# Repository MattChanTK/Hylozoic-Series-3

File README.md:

Hylozoic Series 3 Interactive Control System
======================

 Combining techniques in architecture, the arts, electronics, and software, the Living Architecture System Group (LASG) develops interactive art sculptures that engage occupants in an immersive environment. The overarching goal of this research is to develop architectural systems that possess life-like qualities. In the Hylozoic Series kinetic sculptures built by [Philip Beesley Architect Inc.](http://philipbeesleyarchitect.com/), the designers use a network of microcontrollers to control and sample a sizable number of actuators and sensors. Each node in the network can perform a simple set of interactive behaviours. Though complexity may emerge in previous systems through superposition of a set of simple and prescripted behaviours, the responses of the systems to occupants remain rather robotic and ultimately dictated by the will of the designers. 

To enable the sculpture to automatically generate interactive behaviours and
adapt to changes, [Curiosity-Based Learning Algorithm (CBLA)](https://ece.uwaterloo.ca/~dkulic/pubs/ChanIROS2015.pdf), a reinforcement learning algorithm which selects actions that lead to maximum potential knowledge gains, is introduced.

To realize the CBLA system on a physical interactive art sculpture, an overhaul of the previous series’ interactive control hardware was necessary. CBLA requires the system to be able to sense the consequences of its own actions and its surrounding at a much higher resolution and frequency than previously implemented behaviour algorithms. This translates to the need to interface and collect samples from a substantially larger number of sensors. 

The **Hylozoic Series 3 Interactive Control System** consists of a new set of hardware and control system software was developed. It enables the control and sampling of hundreds of devices on a centralized computer through USB connections. Moving the computation from an embedded platform simpliﬁes the implementation of the CBLA system, which is a computationally intensive and complex
program. In addition, the large amount of data generated by the system can now be recorded without sacriﬁcing response time nor resolution.

## Organizations

### Hardware

The electronics that interface with the sensors and actuators were mostly customly designed. The [schematic](Hardware/Design Files), [PCB design](Hardware/Design Files), BOM, as well as [fabrication files](Hardware/fabrication) (like Gerber and quotes) for previous production runs can be found in the [Hardware](Hardware) directory. 

### Software

The [firmware](Software/teensy_firmware) that runs on the Teensy microcontroller, the [Python-based software framework](Software/pyHylozoic3) (pyHylozoic3), and [installation-specific behaviours](Software/complex_behaviours) can be found in the [Software](Software) directory. In addition, some of the necessary [libraries](Software/_libraries), and some [basic demo codes](Software/basic_behaviours) can also be in the directory.

In addition to the [communication framework](Software/pyHylozoic3/interactive_system/interactive_system), the pyHylozoic3 module includes an implemenation of the [CBLA Engine](Software/pyHylozoic3/cbla/cbla/cbla_engine), and [Abstract Node system](Software/pyHylozoic3/abstract_node/abstract_node) that supports the deployments of a network of multiple [CBLA Nodes](Software/pyHylozoic3/cbla/cbla).

## Contributors
* Matthew Tsz Kiu Chan (University of Waterloo)
* Mohammedreza Memarian (University of Waterloo)
* Matt Borland (Philip Beesley Architect Inc.)
* David Kadish (Philip Beesley Architect Inc.)

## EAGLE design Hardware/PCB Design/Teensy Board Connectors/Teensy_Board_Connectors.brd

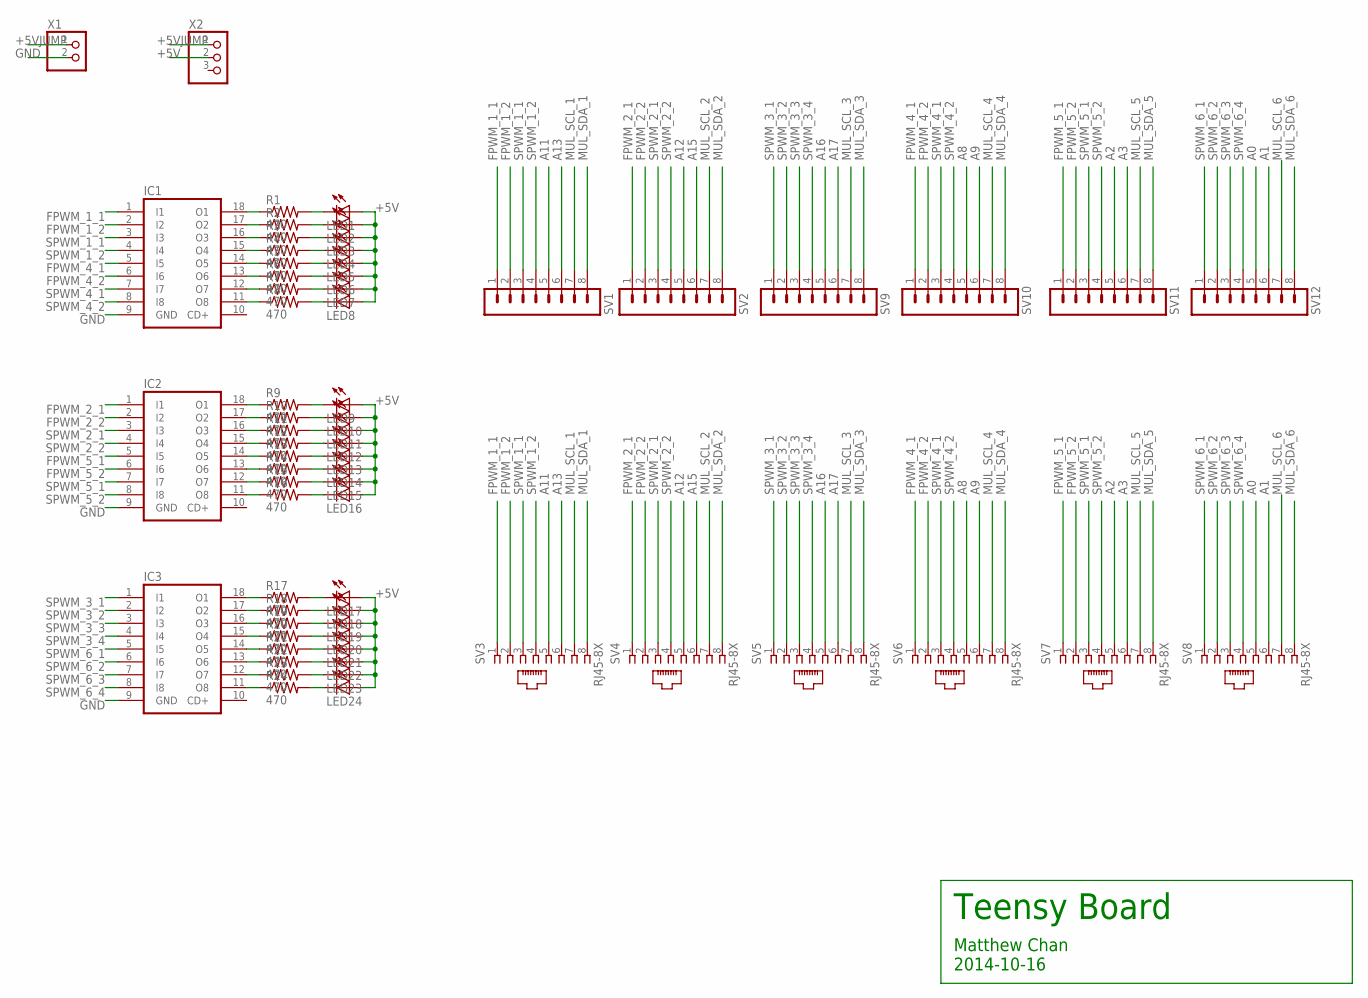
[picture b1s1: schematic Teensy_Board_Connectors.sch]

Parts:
IC1, IC2, IC3: ULN2803AFWG; SOP18
LED1, LED2, LED3, LED4, LED5, LED6, LED7, LED8, LED9, LED10, LED11, LED12, LED13, LED14, LED15, LED16, LED17, LED18, LED19, LED20, LED21, LED22, LED23, LED24: LEDSML1206; SML1206
R1, R2, R3, R4, R5, R6, R7, R8, R9, R10, R11, R12, R13, R14, R15, R16, R17, R18, R19, R20, R21, R22, R23, R24: 470; R0603
SV1, SV2, SV9, SV10, SV11, SV12: MA08-1
SV3, SV4, SV5, SV6, SV7, SV8: RJ45-8X; RJ45-NO-SHIELD
X1: PINHD-1X2; 1X02
X2: PINHD-1X3; 1X03

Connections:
+5V: LED1.A, LED2.A, LED3.A, LED4.A, LED5.A, LED6.A, LED7.A, LED8.A, LED9.A, LED10.A, LED11.A, LED12.A, LED13.A, LED14.A, LED15.A, LED16.A, LED17.A, LED18.A, LED19.A, LED20.A, LED21.A, LED22.A, LED23.A, LED24.A, X2.2
+5VJUMP: X1.1, X2.1
A0: SV8.5, SV12.5
A1: SV8.6, SV12.6
A2: SV7.5, SV11.5
A3: SV7.6, SV11.6
A8: SV6.5, SV10.5
A9: SV6.6, SV10.6
A11: SV1.5, SV3.5
A12: SV2.5, SV4.5
A13: SV1.6, SV3.6
A15: SV2.6, SV4.6
A16: SV5.5, SV9.5
A17: SV5.6, SV9.6
FPWM_1_1: IC1.1 (I1), SV1.1, SV3.1
FPWM_1_2: IC1.2 (I2), SV1.2, SV3.2
FPWM_2_1: IC2.1 (I1), SV2.1, SV4.1
FPWM_2_2: IC2.2 (I2), SV2.2, SV4.2
FPWM_4_1: IC1.5 (I5), SV6.1, SV10.1
FPWM_4_2: IC1.6 (I6), SV6.2, SV10.2
FPWM_5_1: IC2.5 (I5), SV7.1, SV11.1
FPWM_5_2: IC2.6 (I6), SV7.2, SV11.2
GND: IC1.9 (GND), IC2.9 (GND), IC3.9 (GND), X1.2
MUL_SCL_1: SV1.7, SV3.7
MUL_SCL_2: SV2.7, SV4.7
MUL_SCL_3: SV5.7, SV9.7
MUL_SCL_4: SV6.7, SV10.7
MUL_SCL_5: SV7.7, SV11.7
MUL_SCL_6: SV8.7, SV12.7
MUL_SDA_1: SV1.8, SV3.8
MUL_SDA_2: SV2.8, SV4.8
MUL_SDA_3: SV5.8, SV9.8
MUL_SDA_4: SV6.8, SV10.8
MUL_SDA_5: SV7.8, SV11.8
MUL_SDA_6: SV8.8, SV12.8
unnamed: IC1.18 (O1), R1.1
unnamed: LED1.C, R1.2
unnamed: IC1.17 (O2), R2.1
unnamed: IC1.16 (O3), R3.1
unnamed: IC1.15 (O4), R4.1
unnamed: IC1.14 (O5), R5.1
unnamed: IC1.13 (O6), R6.1
unnamed: IC1.12 (O7), R7.1
unnamed: IC1.11 (O8), R8.1
unnamed: LED2.C, R2.2
unnamed: LED3.C, R3.2
unnamed: LED4.C, R4.2
unnamed: LED5.C, R5.2
unnamed: LED6.C, R6.2
unnamed: LED7.C, R7.2
unnamed: LED8.C, R8.2
unnamed: IC2.18 (O1), R9.1
unnamed: LED9.C, R9.2
unnamed: IC2.17 (O2), R10.1
unnamed: IC2.16 (O3), R11.1
unnamed: IC2.15 (O4), R12.1
unnamed: IC2.14 (O5), R13.1
unnamed: IC2.13 (O6), R14.1
unnamed: IC2.12 (O7), R15.1
unnamed: IC2.11 (O8), R16.1
unnamed: LED10.C, R10.2
unnamed: LED11.C, R11.2
unnamed: LED12.C, R12.2
unnamed: LED13.C, R13.2
unnamed: LED14.C, R14.2
unnamed: LED15.C, R15.2
unnamed: LED16.C, R16.2
unnamed: IC3.18 (O1), R17.1
unnamed: LED17.C, R17.2
unnamed: IC3.17 (O2), R18.1
unnamed: IC3.16 (O3), R19.1
unnamed: IC3.15 (O4), R20.1
unnamed: IC3.14 (O5), R21.1
unnamed: IC3.13 (O6), R22.1
unnamed: IC3.12 (O7), R23.1
unnamed: IC3.11 (O8), R24.1
unnamed: LED18.C, R18.2
unnamed: LED19.C, R19.2
unnamed: LED20.C, R20.2
unnamed: LED21.C, R21.2
unnamed: LED22.C, R22.2
unnamed: LED23.C, R23.2
unnamed: LED24.C, R24.2
SPWM_1_1: IC1.3 (I3), SV1.3, SV3.3
SPWM_1_2: IC1.4 (I4), SV1.4, SV3.4
SPWM_2_1: IC2.3 (I3), SV2.3, SV4.3
SPWM_2_2: IC2.4 (I4), SV2.4, SV4.4
SPWM_3_1: IC3.1 (I1), SV5.1, SV9.1
SPWM_3_2: IC3.2 (I2), SV5.2, SV9.2
SPWM_3_3: IC3.3 (I3), SV5.3, SV9.3
SPWM_3_4: IC3.4 (I4), SV5.4, SV9.4
SPWM_4_1: IC1.7 (I7), SV6.3, SV10.3
SPWM_4_2: IC1.8 (I8), SV6.4, SV10.4
SPWM_5_1: IC2.7 (I7), SV7.3, SV11.3
SPWM_5_2: IC2.8 (I8), SV7.4, SV11.4
SPWM_6_1: IC3.5 (I5), SV8.1, SV12.1
SPWM_6_2: IC3.6 (I6), SV8.2, SV12.2
SPWM_6_3: IC3.7 (I7), SV8.3, SV12.3
SPWM_6_4: IC3.8 (I8), SV8.4, SV12.4

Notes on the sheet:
Teensy Board
Matthew Chan 2014-10-16

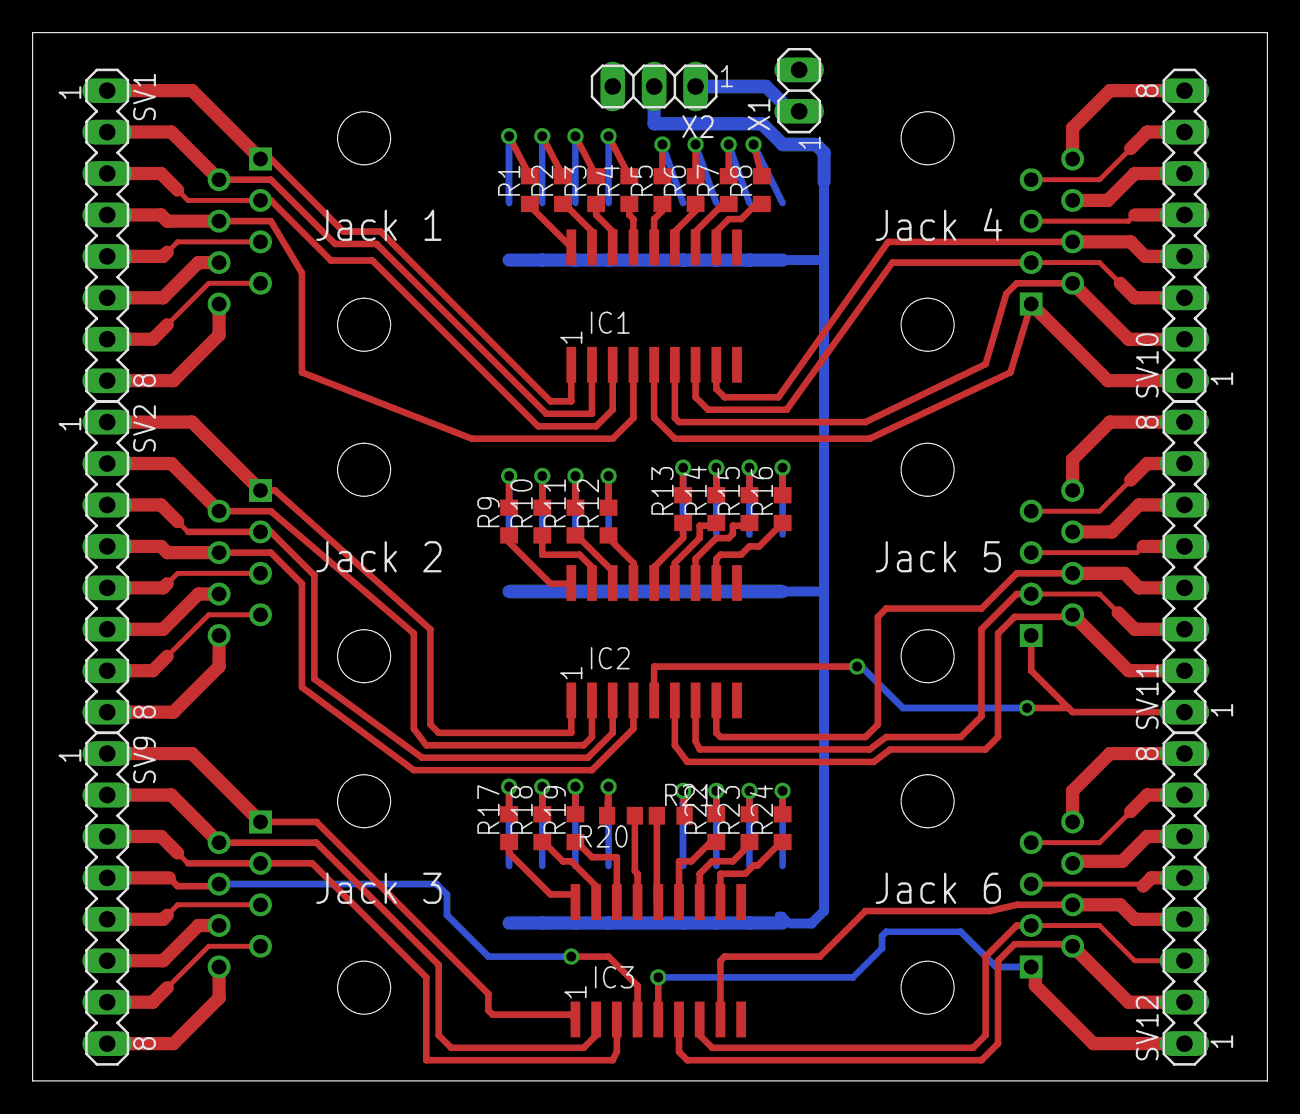
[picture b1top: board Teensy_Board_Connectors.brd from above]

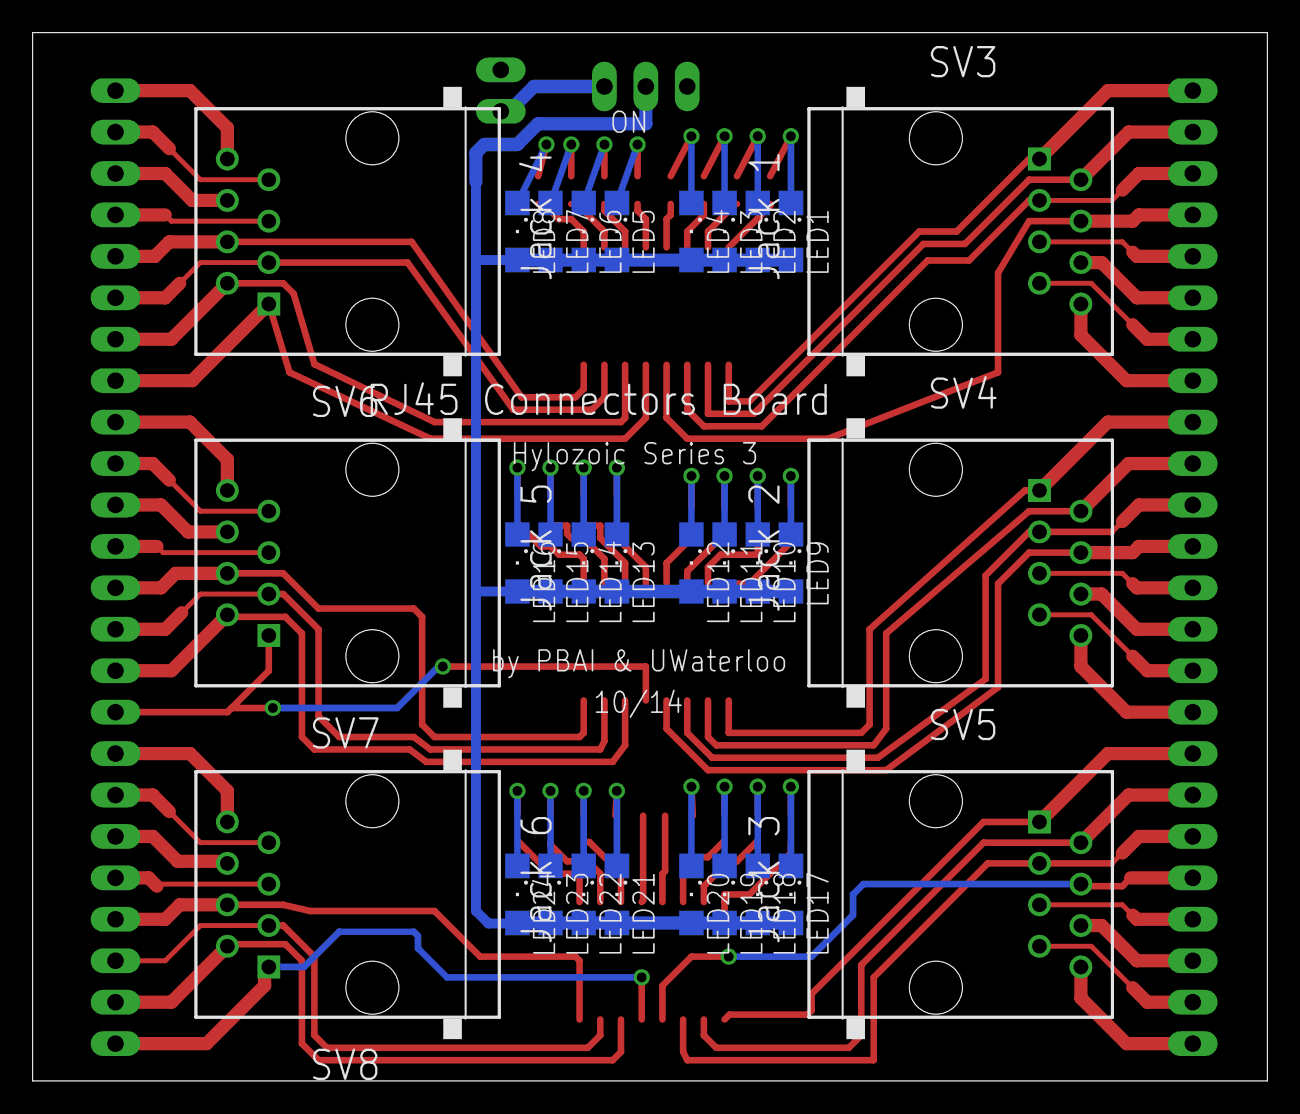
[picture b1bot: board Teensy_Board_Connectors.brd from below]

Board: 2 copper layers, 75.7 x 64.3 mm, 65 parts (30 on the bottom side), 99 nets.

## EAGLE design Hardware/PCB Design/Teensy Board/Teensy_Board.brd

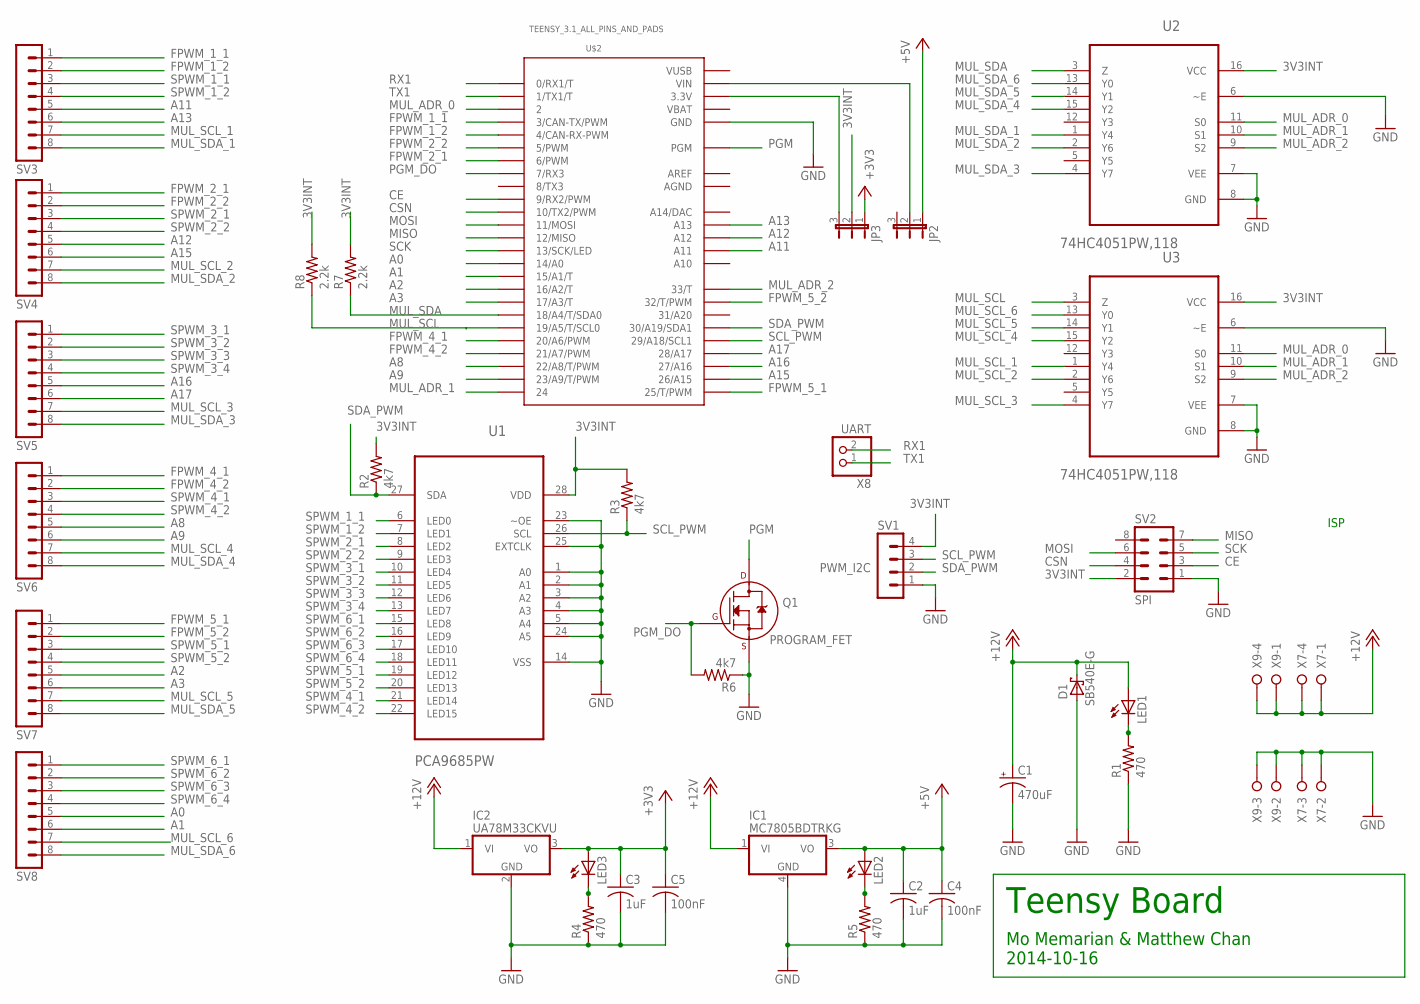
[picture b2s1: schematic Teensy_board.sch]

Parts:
C1: 470uF; E5-10,5
C2, C3: 1uF; C0603
C4, C5: 100nF; C0603
D1: SB540E-G; DO201T15
IC1: MC7805BDTRKG; DPACK_3
IC2: UA78M33CKVU; DPACK
JP2, JP3: JP2E; JP2
LED1, LED2, LED3: LEDSML1206; SML1206
Q1: PROGRAM_FET; SOT-23
R1, R4, R5: 470; R0603
R2, R3, R6: 4k7; R0603
R7, R8: 2.2k; R0603
SV1: PWM_I2C; MA04-1
SV2: SPI; MA04-2
SV3, SV4, SV5, SV6, SV7, SV8: MA08-1
U1: PCA9685PW; SOP65P640X110-28N
U2, U3: 74HC4051PW,118; SOP65P640X110-16N
U$2: TEENSY_3.1_ALL_PINS_AND_PADS; TEENSY_3.1_ALLPINS
X7, X9: W237-04P; W237-4P
X8: UART; 1X02

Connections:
3V3INT: JP3.2, R2.2, R3.2, R7.2, R8.2, SV1.4, SV2.2, U1.28 (VDD), U2.16 (VCC), U3.16 (VCC)
+3V3: C3.1, C5.1, IC2.3 (VO), JP3.1, LED3.A
+5V: C2.1, C4.1, IC1.3 (VO), JP2.1, LED2.A
+12V: C1.+, D1.C, IC1.1 (VI), IC2.1 (VI), LED1.A, X7.1, X7.4, X9.1, X9.4
A0: SV8.5, U$2.14/A0
A1: SV8.6, U$2.15/A1 (15/A1/T)
A2: SV7.5, U$2.16/A2 (16/A2/T)
A3: SV7.6, U$2.17/A3 (17/A3/T)
A8: SV6.5, U$2.22/A8 (22/A8/T/PWM)
A9: SV6.6, U$2.23/A9 (23/A9/T/PWM)
A11: SV3.5, U$2.A11
A12: SV4.5, U$2.A12
A13: SV3.6, U$2.A13
A15: SV4.6, U$2.26 (26/A15)
A16: SV5.5, U$2.27 (27/A16)
A17: SV5.6, U$2.28 (28/A17)
AGND: U$2.AGND
AREF: U$2.AREF
CE: SV2.3, U$2.9 (9/RX2/PWM)
CSN: SV2.4, U$2.10 (10/TX2/PWM)
FPWM_1_1: SV3.1, U$2.3 (3/CAN-TX/PWM)
FPWM_1_2: SV3.2, U$2.4 (4/CAN-RX-PWM)
FPWM_2_1: SV4.1, U$2.6 (6/PWM)
FPWM_2_2: SV4.2, U$2.5 (5/PWM)
FPWM_4_1: SV6.1, U$2.20/A6 (20/A6/PWM)
FPWM_4_2: SV6.2, U$2.21/A7 (21/A7/PWM)
FPWM_5_1: SV7.1, U$2.25 (25/T/PWM)
FPWM_5_2: SV7.2, U$2.32 (32/T/PWM)
GND: C1.-, C2.2, C3.2, C4.2, C5.2, D1.A, IC1.4 (GND), IC2.2 (GND), Q1.2 (S), R1.1, R4.1, R5.1, R6.1, SV1.1, SV2.1, U1.1 (A0), U1.2 (A1), U1.3 (A2), U1.4 (A3), U1.5 (A4), U1.14 (VSS), U1.23 (~OE), U1.24 (A5), U1.25 (EXTCLK), U2.6 (~E), U2.7 (VEE), U2.8 (GND), U3.6 (~E), U3.7 (VEE), U3.8 (GND), U$2.GND, U$2.GND1 (GND), U$2.GND2 (GND), X7.2, X7.3, X9.2, X9.3; also elsewhere on the board
MISO: SV2.7, U$2.12 (12/MISO)
MOSI: SV2.6, U$2.11 (11/MOSI)
MUL_ADR_0: U2.11 (S0), U3.11 (S0), U$2.2
MUL_ADR_1: U2.10 (S1), U3.10 (S1), U$2.24
MUL_ADR_2: U2.9 (S2), U3.9 (S2), U$2.33 (33/T)
MUL_SCL: R8.1, U3.3 (Z), U$2.19/A5 (19/A5/T/SCL0)
MUL_SCL_1: SV3.7, U3.1 (Y4)
MUL_SCL_2: SV4.7, U3.2 (Y6)
MUL_SCL_3: SV5.7, U3.4 (Y7)
MUL_SCL_4: SV6.7, U3.15 (Y2)
MUL_SCL_5: SV7.7, U3.14 (Y1)
MUL_SCL_6: SV8.7, U3.13 (Y0)
MUL_SDA: R7.1, U2.3 (Z), U$2.18/A4 (18/A4/T/SDA0)
MUL_SDA_1: SV3.8, U2.1 (Y4)
MUL_SDA_2: SV4.8, U2.2 (Y6)
MUL_SDA_3: SV5.8, U2.4 (Y7)
MUL_SDA_4: SV6.8, U2.15 (Y2)
MUL_SDA_5: SV7.8, U2.14 (Y1)
MUL_SDA_6: SV8.8, U2.13 (Y0)
unnamed: LED1.C, R1.2
unnamed: LED3.C, R4.2
unnamed: LED2.C, R5.2
PGM: Q1.3 (D), U$2.PGM
PGM_DO: Q1.1 (G), R6.2, U$2.7 (7/RX3)
RX1: U$2.0 (0/RX1/T), X8.2
SCK: SV2.5, U$2.13 (13/SCK/LED)
SCL_PWM: R3.1, SV1.3, U1.26 (SCL), U$2.29 (29/A18/SCL1)
SDA_PWM: R2.1, SV1.2, U1.27 (SDA), U$2.30 (30/A19/SDA1)
SPWM_1_1: SV3.3, U1.6 (LED0)
SPWM_1_2: SV3.4, U1.7 (LED1)
SPWM_2_1: SV4.3, U1.8 (LED2)
SPWM_2_2: SV4.4, U1.9 (LED3)
SPWM_3_1: SV5.1, U1.10 (LED4)
SPWM_3_2: SV5.2, U1.11 (LED5)
SPWM_3_3: SV5.3, U1.12 (LED6)
SPWM_3_4: SV5.4, U1.13 (LED7)
SPWM_4_1: SV6.3, U1.21 (LED14)
SPWM_4_2: SV6.4, U1.22 (LED15)
SPWM_5_1: SV7.3, U1.19 (LED12)
SPWM_5_2: SV7.4, U1.20 (LED13)
SPWM_6_1: SV8.1, U1.15 (LED8)
SPWM_6_2: SV8.2, U1.16 (LED9)
SPWM_6_3: SV8.3, U1.17 (LED10)
SPWM_6_4: SV8.4, U1.18 (LED11)
TEENSY_3V3: JP3.3, U$2.3.3V, U$2.3.3V1 (3.3V), U$2.3.3V2 (3.3V)
TEENSY_VIN: JP2.2, U$2.VIN; also elsewhere on the board
TX1: U$2.1 (1/TX1/T), X8.1
VBAT: U$2.VBAT
VUSB: U$2.VUSB

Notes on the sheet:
Teensy Board
Mo Memarian & Matthew Chan 2014-10-16
ISP

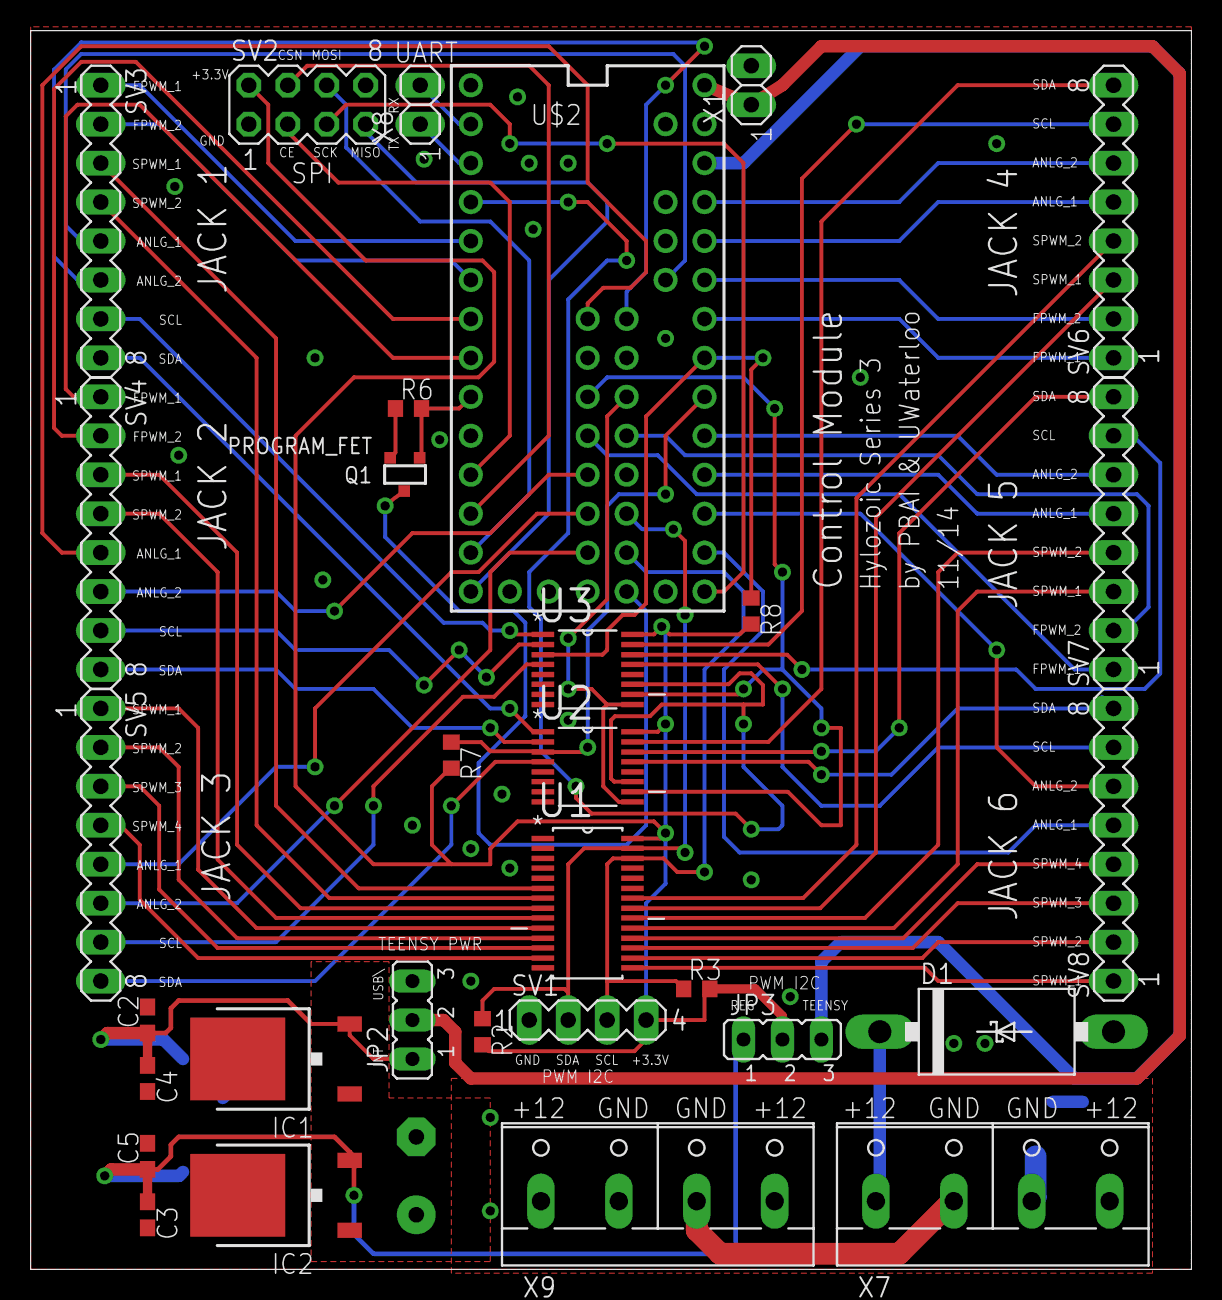
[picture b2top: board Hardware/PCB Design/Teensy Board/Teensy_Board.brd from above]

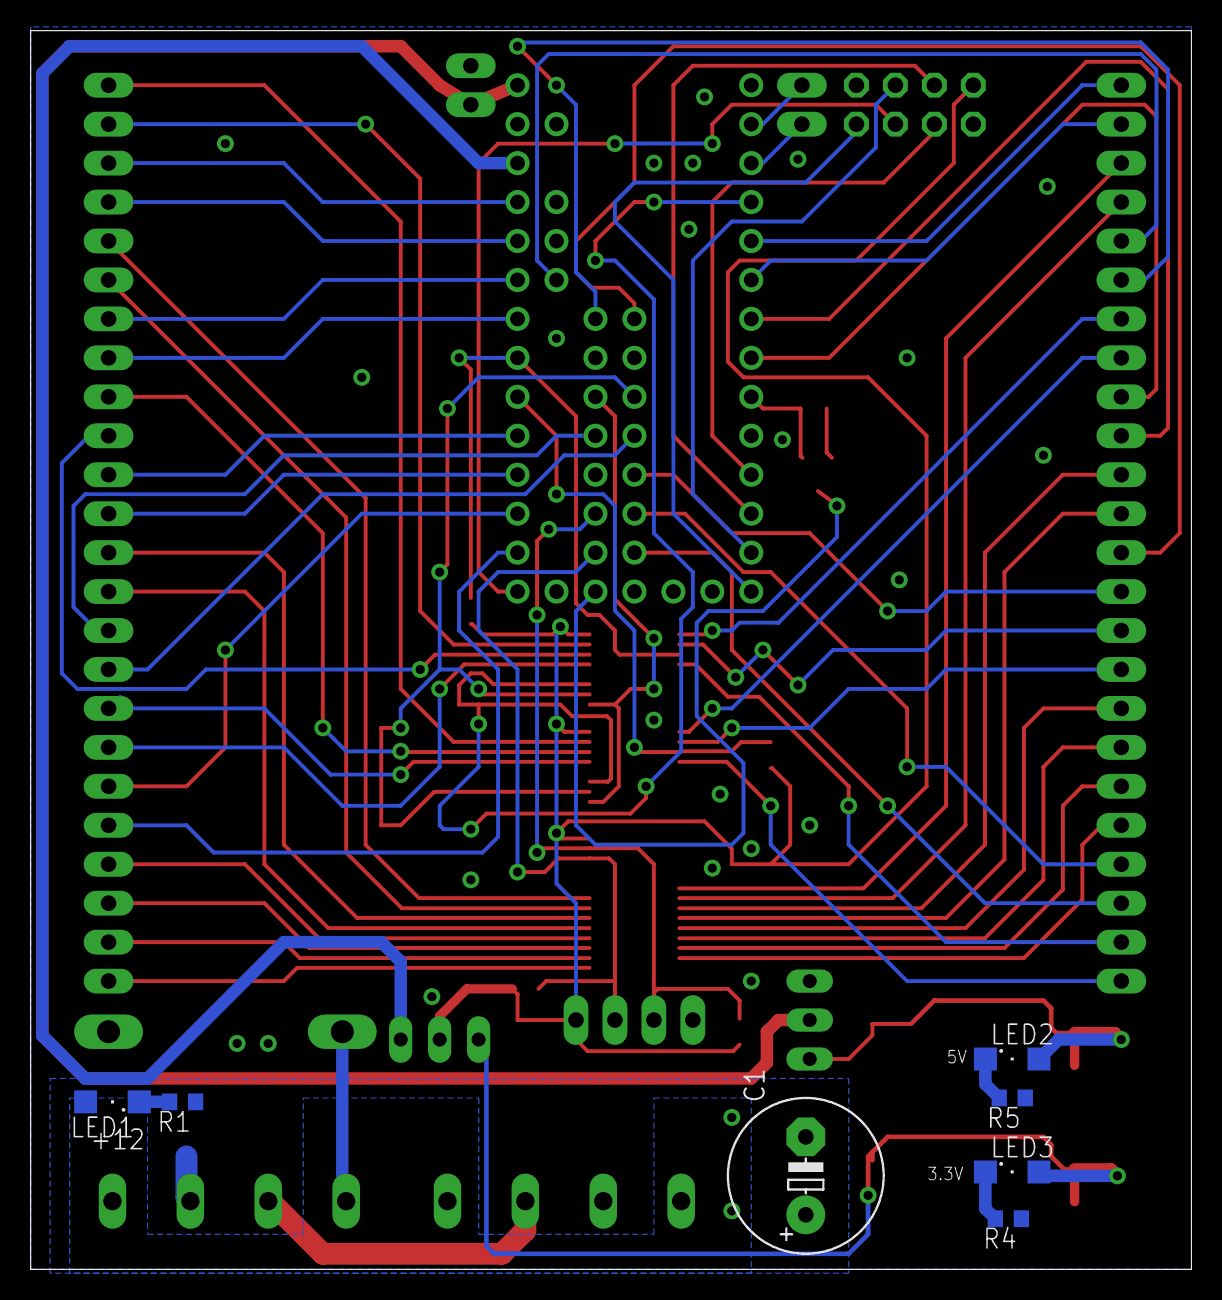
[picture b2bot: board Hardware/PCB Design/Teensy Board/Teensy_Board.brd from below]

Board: 2 copper layers, 75.7 x 80.8 mm, 38 parts (7 on the bottom side), 74 nets.

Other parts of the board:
X1: 1X02

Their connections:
GND: X1.2; also elsewhere on the board
TEENSY_VIN: X1.1; also elsewhere on the board

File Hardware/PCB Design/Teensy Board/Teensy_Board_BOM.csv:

"Qty";"Value";"Device";"Package";"Parts";"Description";"MF";"MPN";"OC_FARNELL";"OC_NEWARK";"PACKAGE";"SUPPLIER";
"2";"";"JP2E";"JP2";"JP2, JP3";"JUMPER";"";"";"";"";"";"";
"3";"";"LEDSML1206";"SML1206";"LED1, LED2, LED3";"LED";"";"";"";"";"";"";
"6";"";"MA08-1";"MA08-1";"SV3, SV4, SV5, SV6, SV7, SV8";"PIN HEADER";"";"";"unknown";"unknown";"";"";
"2";"";"R-US_R0603";"R0603";"R7, R8";"RESISTOR, American symbol";"";"";"";"";"";"";
"3";"";"W237-04P";"W237-4P";"X7, X9, X10";"WAGO SREW CLAMP";"";"";"unknown";"unknown";"";"";
"2";"100nF";"C-USC0603";"C0603";"C4, C5";"CAPACITOR, American symbol";"";"";"";"";"";"";
"2";"1uF";"C-USC0603";"C0603";"C2, C3";"CAPACITOR, American symbol";"";"";"";"";"";"";
"3";"470";"R-US_R0603";"R0603";"R1, R4, R5";"RESISTOR, American symbol";"";"";"";"";"";"";
"1";"470uF";"CPOL-USE5-10.5";"E5-10,5";"C1";"POLARIZED CAPACITOR, American symbol";"";"";"";"";"";"";
"3";"4k7";"R-US_R0603";"R0603";"R2, R3, R6";"RESISTOR, American symbol";"";"";"";"";"";"";
"2";"74HC4051PW,118";"74HC4051PW,118";"SOP65P640X110-16N";"U2, U3";"8-channel analog multiplexer/demultiplexer";"";"74HC4051PW,118";"1826843";"78R6260";"TSSOP-16";"NXP";
"1";"MC7805BDTRKG";"MC7805BDTRKG";"DPACK_3";"IC1";"1A Positive Voltage Regulators";"";"";"";"";"";"";
"1";"PCA9685PW";"PCA9685PW";"SOP65P640X110-28N";"U1";"16-channel, 12-bit PWM Fm+ I2C-bus LED controller";"";"PCA9685PW";"1854074";"19T6398";"TSSOP-28";"NXP";
"1";"PROGRAM_FET";"2N7002_SOT23";"SOT-23";"Q1";"2N7000, 2N7002, NDS7002A";"";"";"";"";"";"";
"1";"PWM_I2C";"MA04-1";"MA04-1";"SV1";"PIN HEADER";"";"";"unknown";"unknown";"";"";
"6";"RJ45-8X";"RJ45-8X";"RJ45-NO-SHIELD";"X1, X2, X3, X4, X5, X6";"CORCOM Modular RJ Jacks No Shield";"";"RJ45-8X";"unknown";"16R6101";"";"";
"1";"SB540E-G";"SB540E-G";"DO201T15";"D1";"SCHOTTKY BARRIER RECTIFIER 3.0 AMPERES 20, 30, 40 VOLT";"";"";"";"";"";"";
"1";"SPI";"MA04-2";"MA04-2";"SV2";"PIN HEADER";"";"";"unknown";"unknown";"";"";
"1";"TEENSY_3.1_ALL_PINS_AND_PADS";"TEENSY_3.1_ALL_PINS_AND_PADS";"TEENSY_3.1_ALLPINS";"U$2";"Footprint for Teensy 3.1 board using all pads and all through-holes. Pads need a 2x7 0.1" SMD header.";"";"";"";"";"";"";
"1";"UA78M33CKVU";"UA78M33CKVU";"DPACK";"IC2";"Linear Voltage Reg";"";"";"";"";"";"";
"1";"UART";"PINHD-1X2";"1X02";"X8";"PIN HEADER";"";"";"";"";"";"";

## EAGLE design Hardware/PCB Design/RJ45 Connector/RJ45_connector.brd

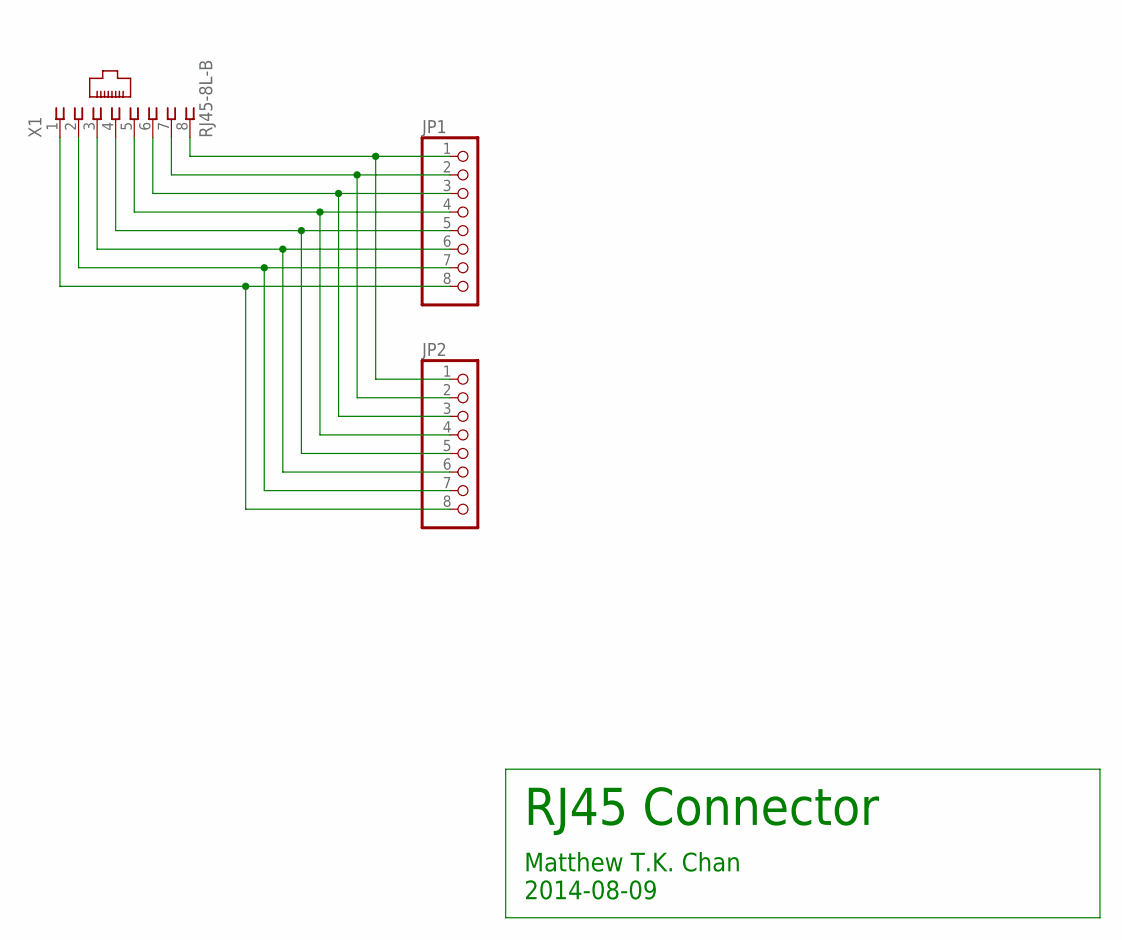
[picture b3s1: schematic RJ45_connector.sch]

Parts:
JP1, JP2: PINHD-1X8/90; 1X08/90
X1: RJ45-8L-B; RJ45-NO-SHIELD

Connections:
unnamed: JP1.1, JP2.1, X1.8
unnamed: JP1.2, JP2.2, X1.7
unnamed: JP1.3, JP2.3, X1.6
unnamed: JP1.4, JP2.4, X1.5
unnamed: JP1.5, JP2.5, X1.4
unnamed: JP1.6, JP2.6, X1.3
unnamed: JP1.7, JP2.7, X1.2
unnamed: JP1.8, JP2.8, X1.1

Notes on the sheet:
RJ45 Connector
Matthew T.K. Chan 2014-08-09

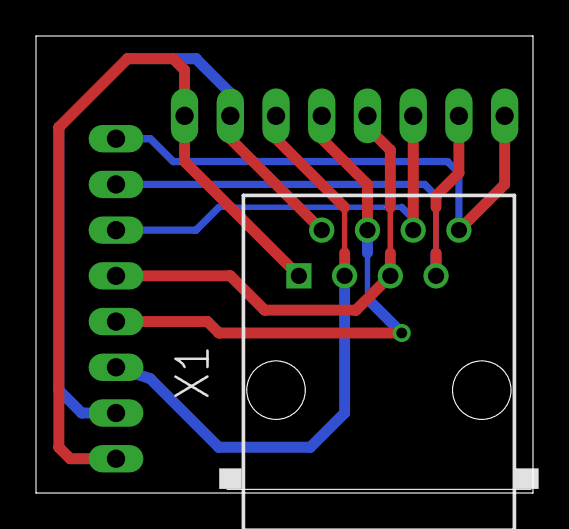
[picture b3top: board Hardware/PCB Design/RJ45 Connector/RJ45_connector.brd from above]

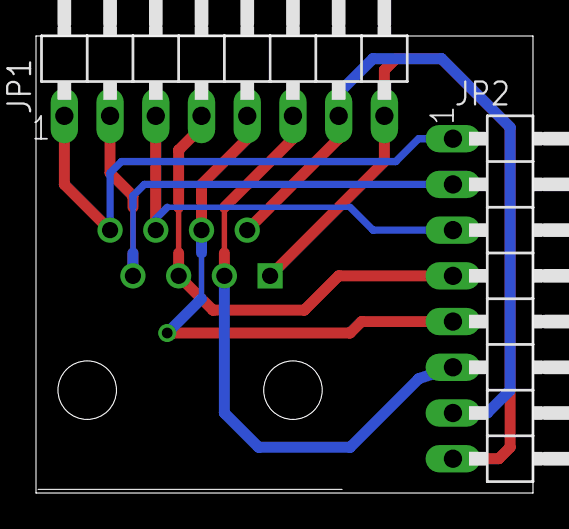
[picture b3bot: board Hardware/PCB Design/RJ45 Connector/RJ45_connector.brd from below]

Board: 2 copper layers, 27.6 x 25.4 mm, 3 parts (2 on the bottom side), 8 nets.

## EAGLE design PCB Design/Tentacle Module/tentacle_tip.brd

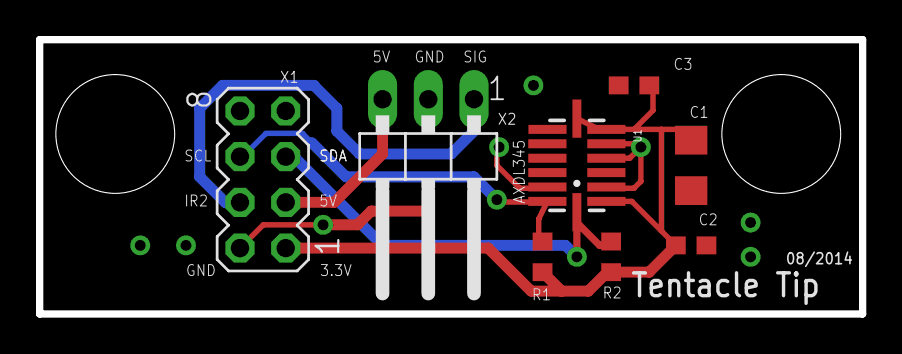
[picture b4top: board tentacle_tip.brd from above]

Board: 2 copper layers, 45.7 x 15.2 mm, 8 parts (0 on the bottom side), 6 nets.

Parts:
C1: 10uF; C1206
C2, C3: 0.1uF; C0603
R1, R2: 2.2k; R0603
U1: ADXL345; LGA14_LONG
X1: MA04-2
X2: 1X03/90

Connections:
+3.3V: C1.1, C2.1, C3.1, R1.2, R2.2, U1.1, U1.6, U1.7, X1.1
+5V: X1.3, X2.3
GND: C1.2, C2.2, C3.2, U1.2, U1.4, U1.5, U1.12, X1.2, X2.2
IR2: X1.4, X2.1
SCL: R2.1, U1.14, X1.5
SDA: R1.1, U1.13, X1.6

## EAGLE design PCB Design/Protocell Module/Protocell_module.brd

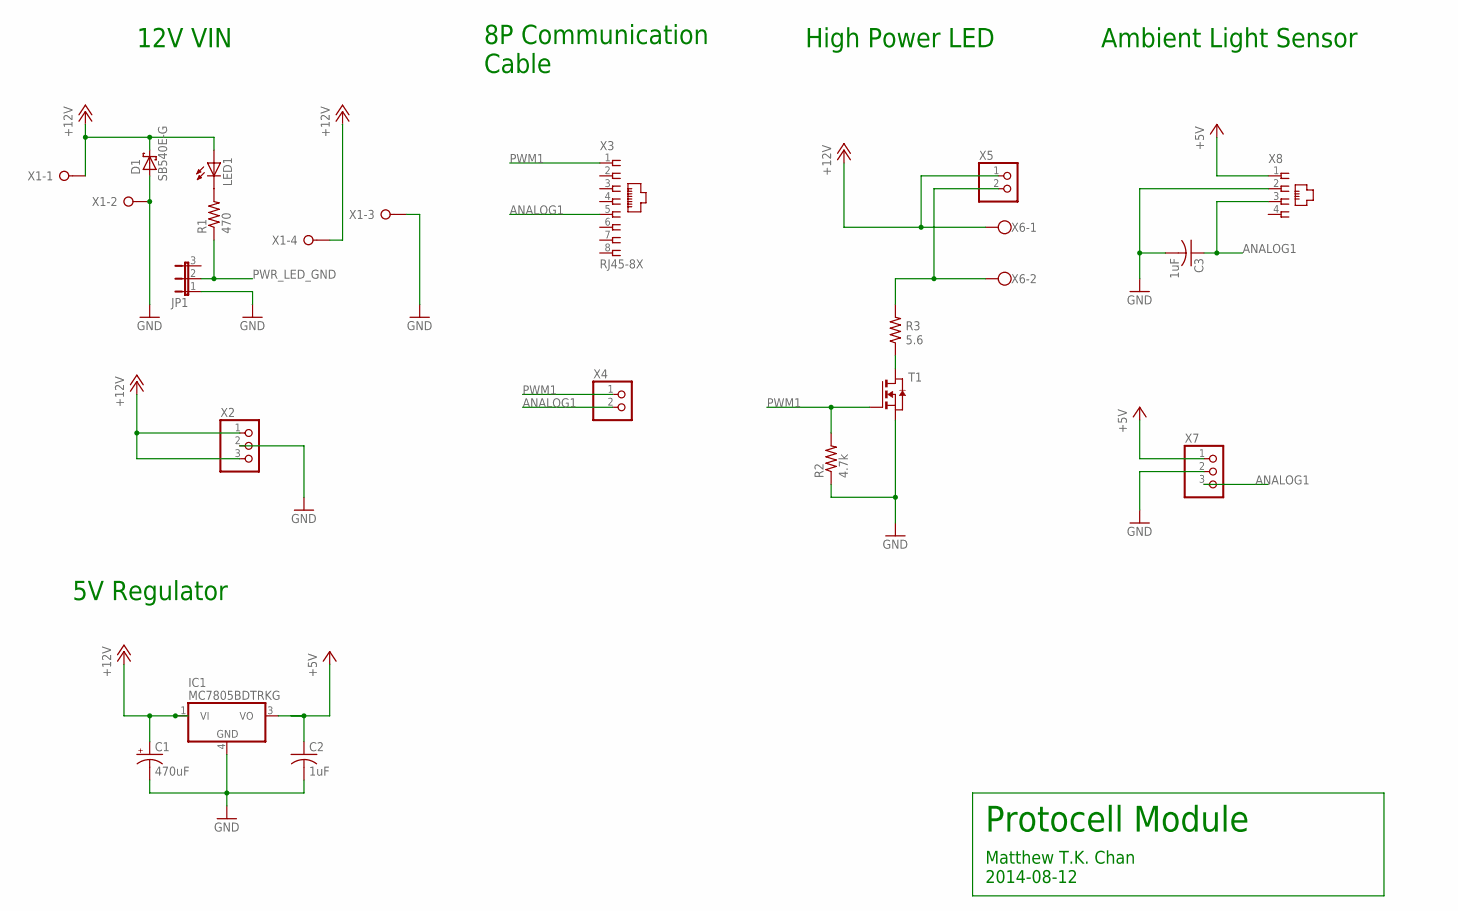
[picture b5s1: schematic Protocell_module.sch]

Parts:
C1: 470uF; E5-10,5
C2, C3: 1uF; C0603
D1: SB540E-G; DO201T15
IC1: MC7805BDTRKG; DPACK_3
JP1: JP2E; JP2
LED1: LEDSML1206; SML1206
R1: 470; R0603
R2: 4.7k; R0603
R3: 5.6; YAGEO_SQP500JB
T1: NTD5867NLT4G; DPACK
X1: W237-04P; W237-4P
X2, X7: PINHD-1X3/90; 1X03/90
X3: RJ45-8X; RJ45-NO-SHIELD
X4, X5: PINHD-1X2/90; 1X02/90
X6: W237-102
X8: 558872-1

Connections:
+5V: C2.1, IC1.3 (VO), X7.1, X8.1
+12V: C1.+, D1.C, IC1.1 (VI), LED1.A, X1.1, X1.4, X2.1, X2.3, X5.1, X6.1
ANALOG1: C3.1, X3.5, X4.2, X7.3, X8.3
GND: C1.-, C2.2, C3.2, D1.A, IC1.4 (GND), JP1.1, R2.1, T1.3 (S), X1.2, X1.3, X2.2, X7.2, X8.2
unnamed: R3.1, T1.2 (D)
unnamed: R3.2, X5.2, X6.2
unnamed: LED1.C, R1.2
PWM1: R2.2, T1.1 (G), X3.1, X4.1
PWR_LED_GND: JP1.2, R1.1

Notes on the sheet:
Protocell Module
Matthew T.K. Chan 2014-08-12
High Power LED
Ambient Light Sensor
12V VIN
5V Regulator
8P Communication Cable

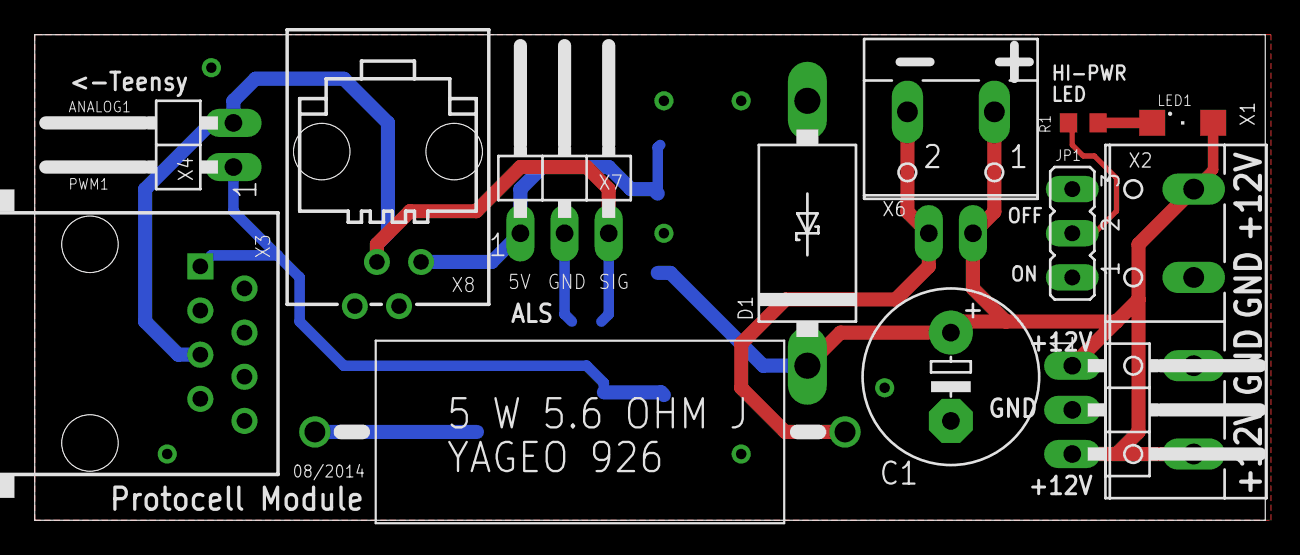
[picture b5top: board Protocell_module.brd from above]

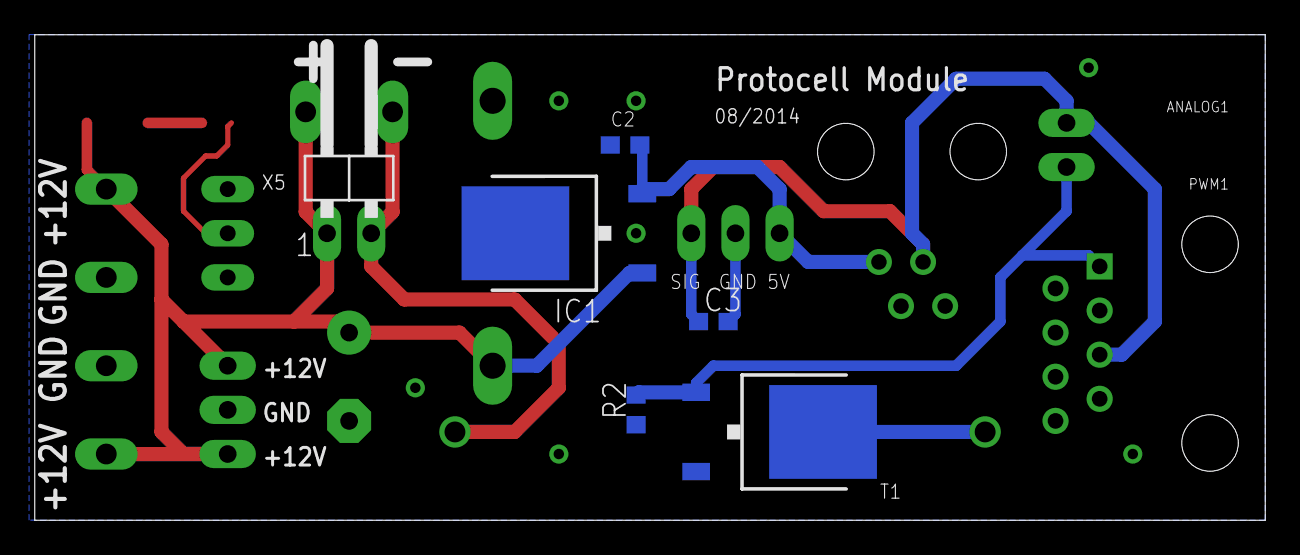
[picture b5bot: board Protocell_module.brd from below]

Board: 2 copper layers, 70.8 x 27.9 mm, 19 parts (6 on the bottom side), 9 nets.
